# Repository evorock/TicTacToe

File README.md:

# TicTacToe
Juego del TicTacToe con Arduino

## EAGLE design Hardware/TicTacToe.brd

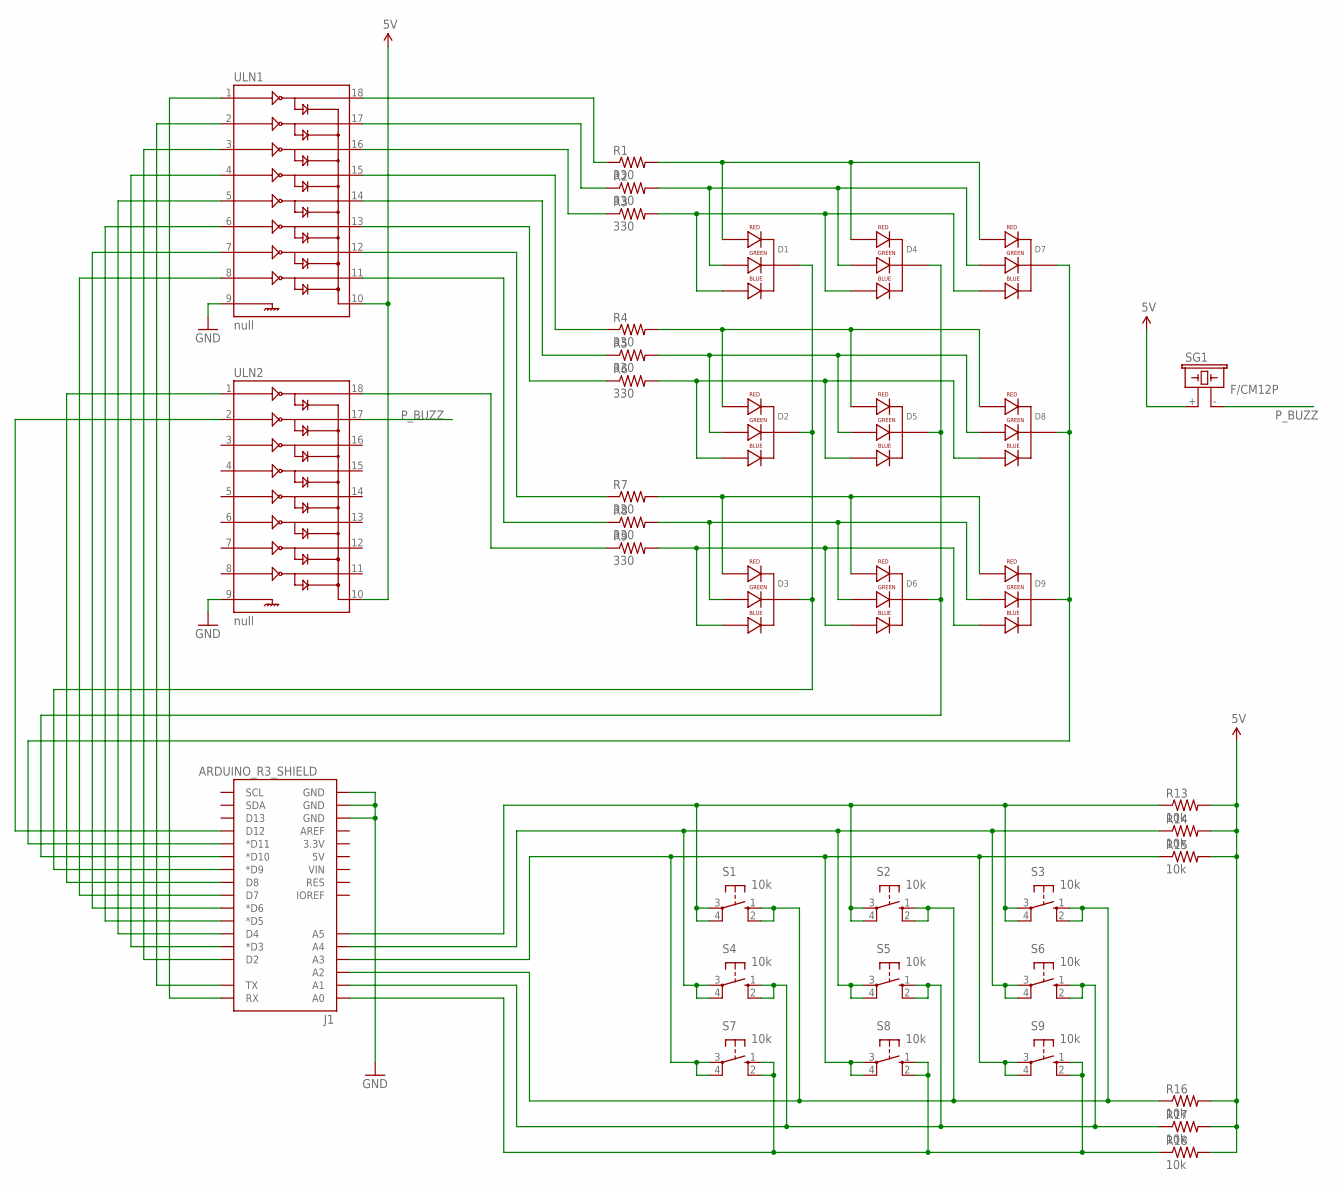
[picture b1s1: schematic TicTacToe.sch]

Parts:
D1, D2, D3, D4, D5, D6, D7, D8, D9: LED-RGB-CC-THRUCLEAR; LED-RGB-THRU
J1: ARDUINO_R3_SHIELD; UNO_R3_SHIELD
R1, R2, R3, R4, R5, R6, R7, R8, R9: 330; 0204/7
R13, R14, R15, R16, R17, R18: 10k; 0204/7
S1, S2, S3, S4, S5, S6, S7, S8, S9: 10k; B3F-10XX
SG1: F/CM12P
ULN1, ULN2: null; DIL18

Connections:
5V: R13.2, R14.2, R15.2, R16.2, R17.2, R18.2, SG1.+ (1), ULN1.10, ULN2.10
GND: J1.GND@0 (GND), J1.GND@1 (GND), J1.GND@2 (GND), ULN1.9, ULN2.9
unnamed: D1.1 (RED_CATHODE), D4.1 (RED_CATHODE), D7.1 (RED_CATHODE), R1.2
unnamed: D1.3 (GREEN_CATHODE), D4.3 (GREEN_CATHODE), D7.3 (GREEN_CATHODE), R2.2
unnamed: D1.4 (BLUE_CATHODE), D4.4 (BLUE_CATHODE), D7.4 (BLUE_CATHODE), R3.2
unnamed: D2.4 (BLUE_CATHODE), D5.4 (BLUE_CATHODE), D8.4 (BLUE_CATHODE), R6.2
unnamed: D2.1 (RED_CATHODE), D5.1 (RED_CATHODE), D8.1 (RED_CATHODE), R4.2
unnamed: D2.3 (GREEN_CATHODE), D5.3 (GREEN_CATHODE), D8.3 (GREEN_CATHODE), R5.2
unnamed: D3.1 (RED_CATHODE), D6.1 (RED_CATHODE), D9.1 (RED_CATHODE), R7.2
unnamed: D3.3 (GREEN_CATHODE), D6.3 (GREEN_CATHODE), D9.3 (GREEN_CATHODE), R8.2
unnamed: D3.4 (BLUE_CATHODE), D6.4 (BLUE_CATHODE), D9.4 (BLUE_CATHODE), R9.2
unnamed: J1.A5, R13.1, S1.3, S1.4 (P1), S2.3, S2.4 (P1), S3.3, S3.4 (P1)
unnamed: J1.A0, R18.1, S7.1 (S), S7.2 (S1), S8.1 (S), S8.2 (S1), S9.1 (S), S9.2 (S1)
unnamed: R1.1, ULN1.18
unnamed: R2.1, ULN1.17
unnamed: R3.1, ULN1.16
unnamed: R4.1, ULN1.15
unnamed: R5.1, ULN1.14
unnamed: R6.1, ULN1.13
unnamed: R7.1, ULN1.12
unnamed: R8.1, ULN1.11
unnamed: R9.1, ULN2.18
unnamed: J1.RX, ULN1.1
unnamed: J1.TX, ULN1.2
unnamed: J1.D8, ULN2.1
unnamed: J1.D2, ULN1.3
unnamed: J1.D3 (*D3), ULN1.4
unnamed: J1.D4, ULN1.5
unnamed: J1.D5 (*D5), ULN1.6
unnamed: J1.D6 (*D6), ULN1.7
unnamed: J1.D7, ULN1.8
unnamed: D1.2 (CATHODE), D2.2 (CATHODE), D3.2 (CATHODE), J1.D9 (*D9)
unnamed: J1.D12, ULN2.2
unnamed: D4.2 (CATHODE), D5.2 (CATHODE), D6.2 (CATHODE), J1.D10 (*D10)
unnamed: D7.2 (CATHODE), D8.2 (CATHODE), D9.2 (CATHODE), J1.D11 (*D11)
unnamed: J1.A1, R17.1, S4.1 (S), S4.2 (S1), S5.1 (S), S5.2 (S1), S6.1 (S), S6.2 (S1)
unnamed: J1.A2, R16.1, S1.1 (S), S1.2 (S1), S2.1 (S), S2.2 (S1), S3.1 (S), S3.2 (S1)
unnamed: J1.A3, R15.1, S7.3, S7.4 (P1), S8.3, S8.4 (P1), S9.3, S9.4 (P1)
unnamed: J1.A4, R14.1, S4.3, S4.4 (P1), S5.3, S5.4 (P1), S6.3, S6.4 (P1)
P_BUZZ: SG1.- (2), ULN2.17

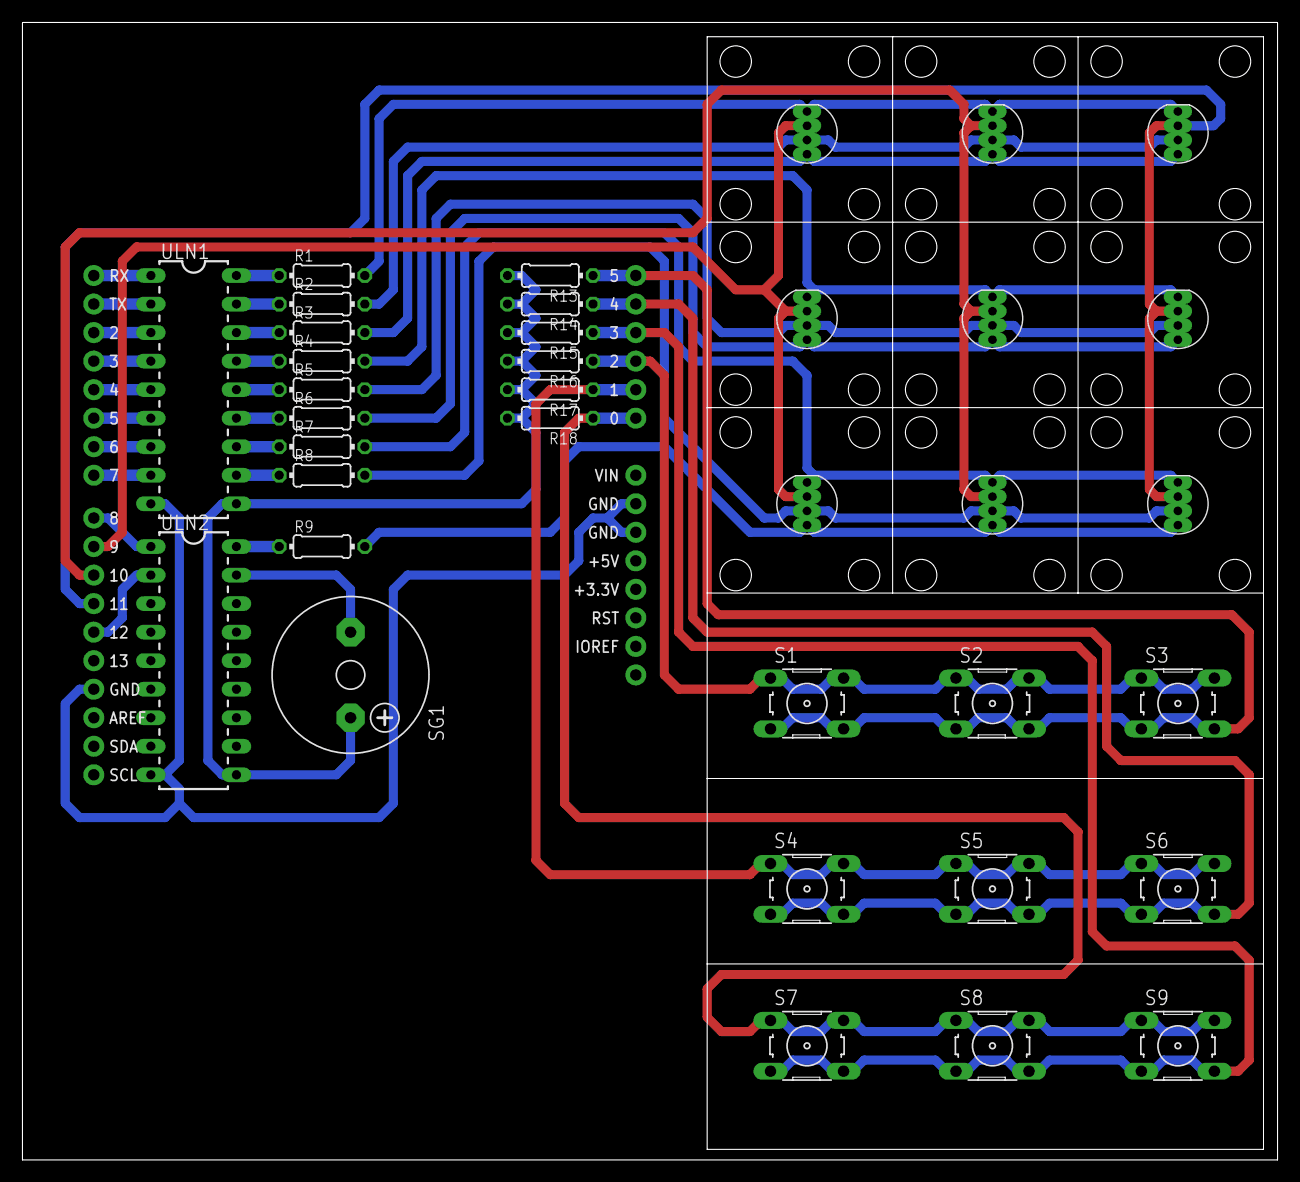
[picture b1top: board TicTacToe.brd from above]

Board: 2 copper layers, 111.7 x 101.3 mm, 37 parts (0 on the bottom side), 40 nets.

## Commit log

2016-09-25 Creacion del proyecti tic tac toe, creando un escudo para arduino uno
2016-09-25 Finalizacion del esquematico y montaje del pcb board, solo falta enrutado y una revision final
2016-09-26 Pequeño enrutado del pcb board
2016-09-26 Finalizacion del enrutado, solo falta reparar la libreria del RGB por overloap

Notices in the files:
parts and their libraries:
SparkFun-LED: Licensing: Creative Commons ShareAlike 4.0 International - https://creativecommons.org/licenses/by-sa/4.0
